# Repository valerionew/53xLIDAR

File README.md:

# 53xLIDAR

## Overview
Project for an opensource, all-in-one, solid state lidar.  
The lidar is made with 16 **VL53L1x** Time-of-flight IR ranging sensors.  

The sensors are operated by an **STM32F411RE** on two separate I2C buses, one for sensor 1-8, the other for 9-16. 
The XSHUTs are shared between two sensors on the two different I2C buses, while the sensors interrupts are separate for each sensor.   
For future use, there is an **LSM9DS1**, 9 DOF inertial sensor onboard.  

The lidar outputs the data via a virtual com port from the native Micro-USB, or via a 3.3V UART on a 4 pin JST-PH connector.  
Power (5V 100mA) is provided through the USB or via the 4 pin uart connector.

## Hardware
The hardware is designed in KiCAD and released under CERN OHL licence. 

It is formed by 16 sensor daughter boards, arranged in a 32 modules panel (only half panel is needed for one lidar, but for manufacturing reasons is made as a 32 modules panel); a bottom board containing all the electronics; a top board which brings the I2C line to the sensors and adds mechanical strenght and protection to the sensors.

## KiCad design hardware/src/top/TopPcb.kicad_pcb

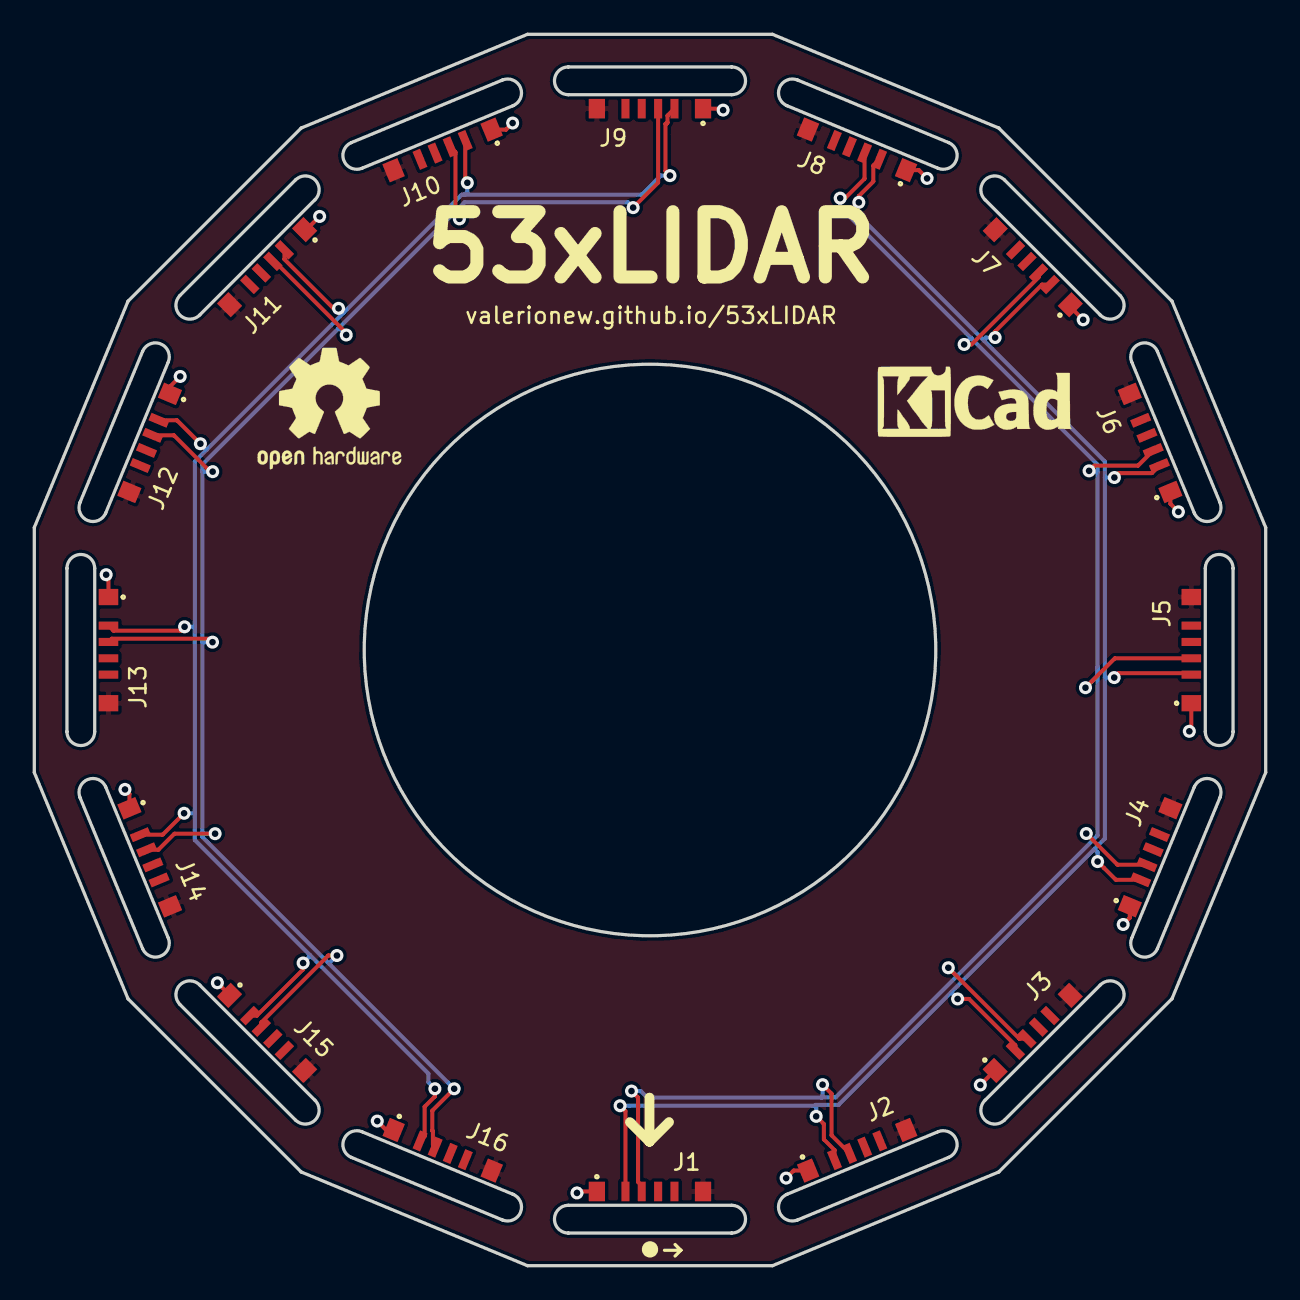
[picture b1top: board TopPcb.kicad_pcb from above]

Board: 2 copper layers, 75.4 x 75.4 mm, 16 parts (0 on the bottom side), 6 nets.

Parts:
J1, J2, J3, J4, J5, J6, J7, J8, J9, J10, J11, J12, J13, J14, J15, J16: CONN_01X06; CONN

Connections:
+3V3: J1.1, J2.1, J3.1, J4.1, J5.1, J6.1, J7.1, J8.1, J9.1, J10.1, J11.1, J12.1, J13.1, J14.1, J15.1, J16.1
GND: J1.6, J2.6, J3.6, J4.6, J5.6, J6.6, J7.6, J8.6, J9.6, J10.6, J11.6, J12.6, J13.6, J14.6, J15.6, J16.6
SCL1: J1.3, J2.3, J3.3, J4.3, J5.3, J6.3, J7.3, J8.3
SCL2: J9.3, J10.3, J11.3, J12.3, J13.3, J14.3, J15.3, J16.3
SDA1: J1.2, J2.2, J3.2, J4.2, J5.2, J6.2, J7.2, J8.2
SDA2: J9.2, J10.2, J11.2, J12.2, J13.2, J14.2, J15.2, J16.2

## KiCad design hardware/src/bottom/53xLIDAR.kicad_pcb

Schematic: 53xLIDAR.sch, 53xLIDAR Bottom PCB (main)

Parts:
BOOT0_TP1: BOOT0; Measurement_Point_Round-SMD-Pad_Small
C1, C2, C3, C4, C5, C6, C7, C8, C12, C13, C17, C20, C22: 100n; C_0402
C9, C14, C15, C16, C18, C19: 4.7u; C_0805_HandSoldering
C10, C11: 15p; C_0402
C21: 10n 16V; C_0805_HandSoldering
D1: USL1M; D_SOD-123
J1, J2, J3, J4, J5, J6, J7, J8, J9, J10, J11, J12, J13, J14, J15, J16: CONN_01X06; CONN
J17: USB_OTG; miniusb_MUSB-B5-S-VT-TSMT-1
J18: UART_EXT; JST_PH_B4B-PH-SM4-TB_04x2.00mm_Straight
J19: I2C1_DEBUG; Pad_test_SMD_1x03_Pitch1.27mm
J20: I2C2_DEBUG; Pad_test_SMD_1x03_Pitch1.27mm
J21: UART_DEBUG; Pad_test_SMD_1x03_Pitch1.27mm
J22: SWD; Pin_Header_Straight_1x04_Pitch2.54mm
J23: SPI1_EXT; JST_PH_B6B-PH-SM4-TB_06x2.00mm_Straight
J25: GS3
R1: 10k; R_0402
U1, U2, U3, U4: WS2812S; LED_WS2812-PLCC6
U5: STM32F411RETx; LQFP-64_10x10mm_Pitch0.5mm
U6: MPU-9250; QFN-24_3x3mm_Pitch0.4mm
U7: KF33_DPAK; TO-252-2
U8: LSM9DS1; LGA-24L_3x3.5mm_Pitch0.43mm
Y1: 24MHz SR PASSIVES 3225-24M-SR; Crystal_SMD_3225-4pin_3.2x2.5mm

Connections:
+3V3: C5.1, C6.1, C7.1, C8.1, C12.2, C15.1, C16.1, C17.1, C18.1, C19.1, C20.2, J1.1, J2.1, J3.1, J4.1, J5.1, J6.1, J7.1, J8.1, J9.1, J10.1, J11.1, J12.1, J13.1, J14.1, J15.1, J16.1, J22.1, J23.1, J25.1, U5.13 (VREF+), U5.19 (VDD), U5.32 (VDD), U5.48 (VDD), U5.64 (VDD), U6.1, U6.8, U6.13, U7.3 (VO), U8.1, U8.3, U8.22, U8.23
EXT_CS: J23.5, U5.53 (PC12/I2S3_SD/SDIO_CK/SPI3_MOSI)
IMU_CS: U5.61 (I2C1_SCL/I2C3_SDA/I2S5_SD/SDIO_D4/SPI5_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), U6.22, U8.7
IMU_CS_MAG: U5.52 (PC11/ADC1_EXTI11/I2S3_ext_SD/SDIO_D3/SP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), U8.8
IMU_DRDY_MAG: U5.34 (I2S2_CK/I2S4_CK/SPI2_SCK/SPI4_SCK/TIM1_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), U8.9
IMU_INT: U5.54 (PD2/SDIO_CMD/TIM3_ETR), U6.12, U8.11
IMU_INT_MAG: U5.51 (PC10/I2S3_CK/SDIO_D2/SPI3_SCK), U8.10
INT1: J1.5, U5.24 (PC4/ADC1_IN14)
INT2: J2.5, U5.25 (PC5/ADC1_IN15)
INT3: J3.5, U5.26 (ADC1_IN8/I2S5_CK/SPI5_SCK/TIM1_CH2N/TIM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)
INT4: J4.5, U5.27 (ADC1_IN9/I2S5_WS/SPI5_NSS/TIM1_CH3N/TIM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)
INT5: J5.5, U5.28 (BOOT1/PB2)
INT6: J6.5, U5.35 (I2S2_ext_SD/SDIO_D6/SPI2_MISO/TIM1_CH2N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)
INT7: J7.5, U5.36 (ADC1_EXTI15/I2S2_SD/RTC_REFIN/SDIO_CK/S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)
INT8: J8.5, U5.37 (PC6/I2S2_MCK/SDIO_D6/TIM3_CH1/USART6_TX)
INT9: J9.5, U5.38 (PC7/I2S2_CK/I2S3_MCK/SDIO_D7/SPI2_SCK/T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)
INT10: J10.5, U5.39 (PC8/SDIO_D0/TIM3_CH3/USART6_CK)
INT11: J11.5, U5.4 (PC15/ADC1_EXTI15/RCC_OSC32_OUT)
INT12: J12.5, U5.2 (PC13/ANTI_TAMP/RTC_AF1)
INT13: J13.5, U5.3 (PC14/RCC_OSC32_IN)
INT14: J14.5, U5.62 (I2C1_SDA/I2C2_SDA/I2S2_WS/SDIO_D5/SPI2_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)
INT15: J15.5, U5.14 (ADC1_IN0/SYS_WKUP/TIM2_CH1/TIM2_ETR/TIM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)
INT16: J16.5, U5.15 (ADC1_IN1/I2S4_SD/SPI4_MOSI/TIM2_CH2/TIM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)
unnamed: BOOT0_TP1.1, R1.1, U5.60 (BOOT0)
unnamed: C9.2, U5.30 (VCAP1)
unnamed: C10.1, U5.5 (PH0/RCC_OSC_IN), Y1.3
unnamed: C11.1, U5.6 (PH1/RCC_OSC_OUT), Y1.1
unnamed: C13.2, U6.10
unnamed: C21.2, U8.21
unnamed: C22.1, U8.24
unnamed: D1.1, U1.3
unnamed: J25.2, U8.13
unnamed: U1.1, U2.2
unnamed: U2.1, U3.2
unnamed: U3.1, U4.2
SCL1: J1.3, J2.3, J3.3, J4.3, J5.3, J6.3, J7.3, J8.3, J19.1, U5.58 (I2C1_SCL/TIM4_CH1/USART1_TX/PB6)
SCL2: J9.3, J10.3, J11.3, J12.3, J13.3, J14.3, J15.3, J16.3, J20.1, U5.29 (I2C2_SCL/I2S2_CK/I2S3_MCK/SDIO_D7/SPI2_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)
SCL_IMU: J23.4, U5.33 (I2C2_SMBA/I2S2_WS/I2S3_CK/I2S4_WS/SPI2_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), U5.41 (I2C3_SCL/RCC_MCO_1/SDIO_D1/TIM1_CH1/USA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), U6.23, U8.2
SDA1: J1.2, J2.2, J3.2, J4.2, J5.2, J6.2, J7.2, J8.2, J19.2, U5.59 (I2C1_SDA/SDIO_D0/TIM4_CH2/USART1_RX/PB7)
SDA2: J9.2, J10.2, J11.2, J12.2, J13.2, J14.2, J15.2, J16.2, J20.2, U5.55 (I2C2_SDA/I2S1_CK/I2S3_CK/SPI1_SCK/SPI3_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)
SDA_IMU: J23.2, U5.40 (PC9/I2C3_SDA/I2S_CKIN/RCC_MCO_2/SDIO_D1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), U5.57 (I2C1_SMBA/I2S1_SD/I2S3_SD/SDIO_D3/SPI1_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), U6.24, U8.4
SPI1_MISO: J23.3, U5.56 (I2C3_SDA/I2S3_ext_SD/SDIO_D0/SPI1_MISO/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), U6.9, U8.5, U8.6
SWCLK_PROGRAMMING: J22.3, U5.49 (SYS_JTCK-SWCLK/PA14)
SWDIO_PROGRAMMING: J22.2, U5.46 (SYS_JTMS-SWDIO/PA13)
USART_DEBUG_RX: J21.1, U5.17 (ADC1_IN3/I2S2_MCK/TIM2_CH4/TIM5_CH4/TIM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)
USART_DEBUG_TX: J21.2, U5.16 (ADC1_IN2/I2S_CKIN/TIM2_CH3/TIM5_CH3/TIM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)
USART_EXT_RX: J18.2, U5.43 (I2S5_SD/SPI5_MOSI/TIM1_CH3/USART1_RX/US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)
USART_EXT_TX: J18.1, U5.42 (I2C3_SMBA/SDIO_D2/TIM1_CH2/USART1_TX/US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)
USB_D+: J17.3, U5.45 (SPI5_MISO/TIM1_ETR/USART1_RTS/USART6_RX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)
USB_D-: J17.2, U5.44 (ADC1_EXTI11/SPI4_MISO/TIM1_CH4/USART1_C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)
USB_VBUS: C1.1, C2.1, C3.1, C4.1, C14.1, D1.2, J17.1, J18.3, U1.5, U2.3, U2.5, U3.3, U3.5, U4.3, U4.5, U7.1 (VI)
WS2812S_DATA: U1.2, U5.50 (ADC1_EXTI15/I2S1_WS/I2S3_WS/SPI1_NSS/SP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)
XSHUT1: J8.4, J9.4, U5.8 (PC0/ADC1_IN10)
XSHUT2: J7.4, J10.4, U5.9 (PC1/ADC1_IN11)
XSHUT3: J6.4, J11.4, U5.10 (PC2/ADC1_IN12/I2S2_ext_SD/SPI2_MISO)
XSHUT4: J5.4, J12.4, U5.11 (PC3/ADC1_IN13/I2S2_SD/SPI2_MOSI)
XSHUT5: J4.4, J13.4, U5.20 (ADC1_IN4/I2S1_WS/I2S3_WS/SPI1_NSS/SPI3_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)
XSHUT6: J3.4, J14.4, U5.21 (ADC1_IN5/I2S1_CK/SPI1_SCK/TIM2_CH1/TIM2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)
XSHUT7: J2.4, J15.4, U5.22 (ADC1_IN6/I2S2_MCK/SDIO_CMD/SPI1_MISO/TI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)
XSHUT8: J1.4, J16.4, U5.23 (ADC1_IN7/I2S1_SD/SPI1_MOSI/TIM1_CH1N/TI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)

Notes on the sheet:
SET THE UNUSED ONE TO HIGH IMPEDANCE

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
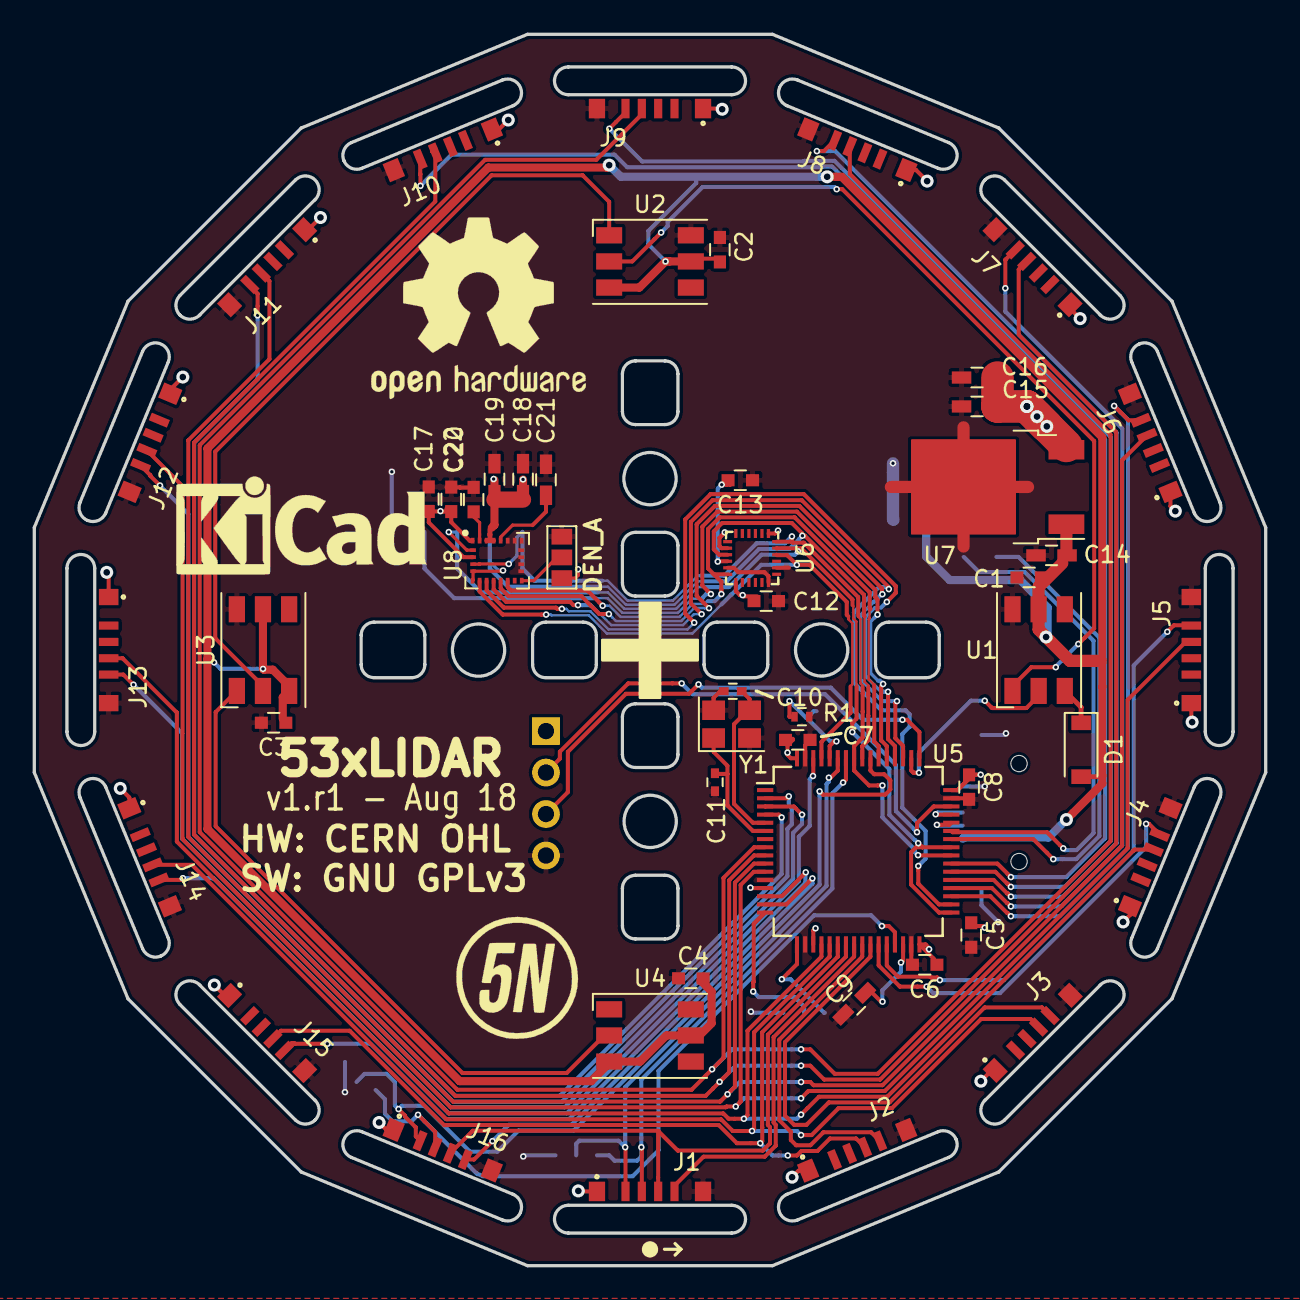
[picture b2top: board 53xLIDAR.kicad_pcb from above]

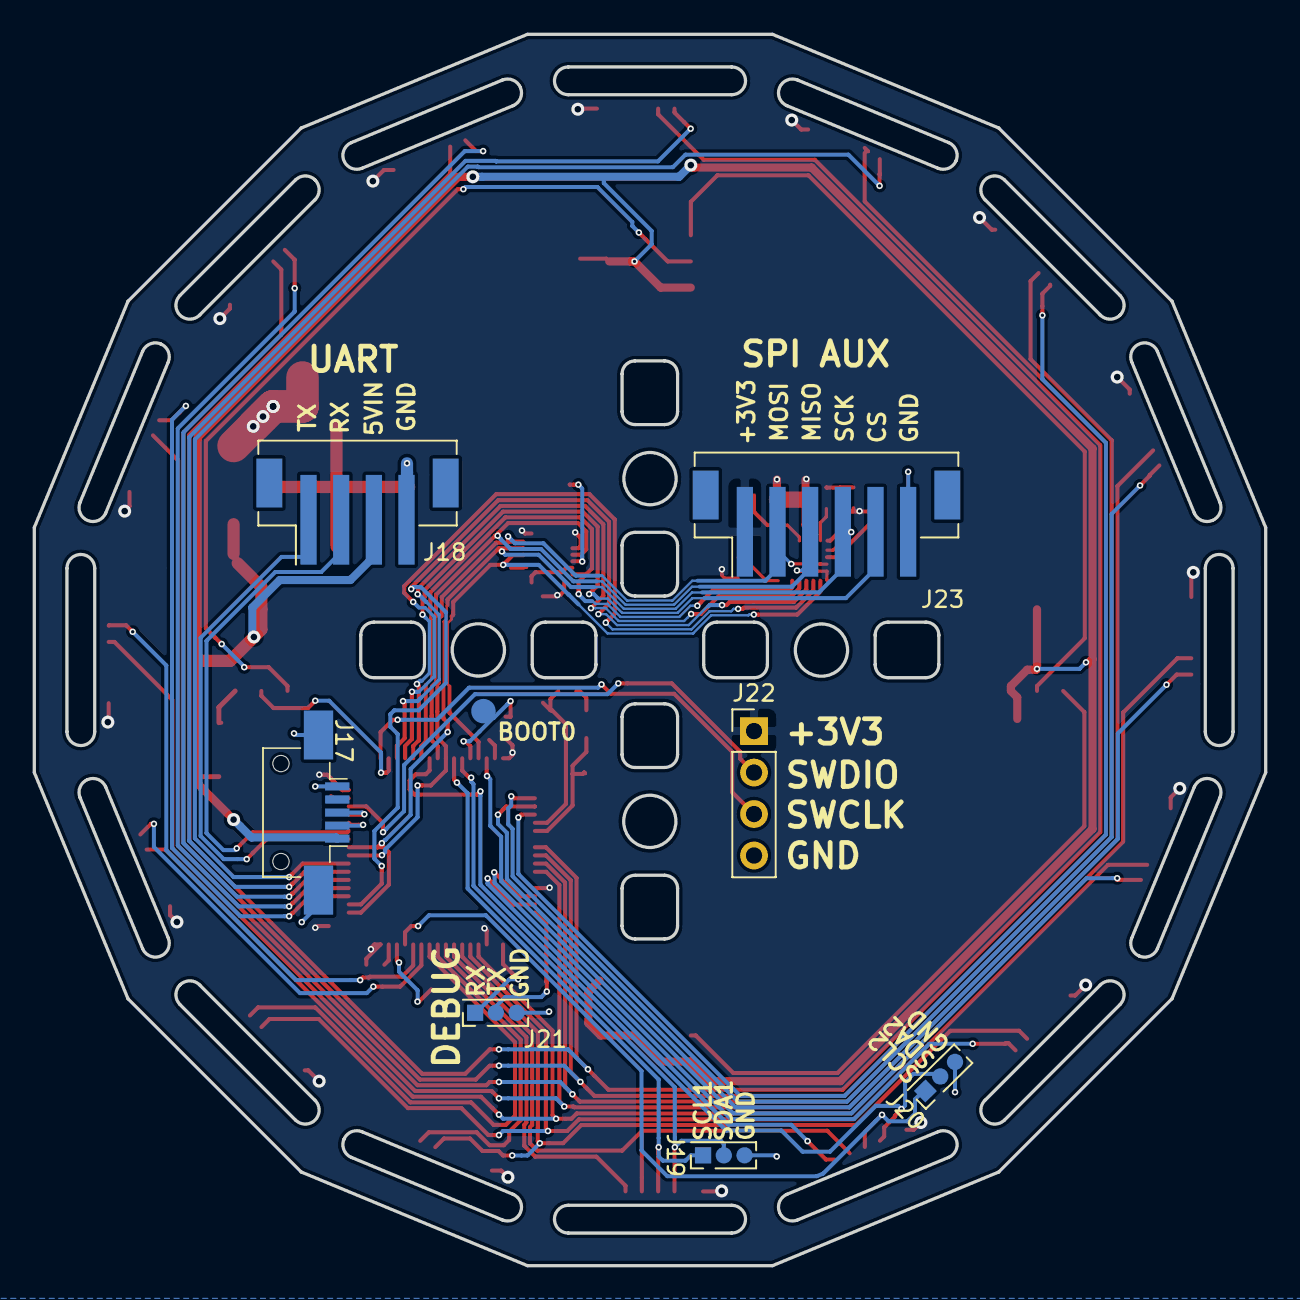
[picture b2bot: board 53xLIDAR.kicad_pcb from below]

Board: 2 copper layers, 75.4 x 75.4 mm, 58 parts (8 on the bottom side), 61 nets.

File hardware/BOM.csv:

Id,Ref,Package,Quantity,Value
1,C21,C_0603_HandSoldering,1,10n 16V
3,J17,USB_Mini-B_AdamTech_MUSB-B5-S-VT-TSMT-1_SMD_Vertical,1,USB_OTG
5,U5,LQFP-64_10x10mm_Pitch0.5mm,1,STM32F411RETx
7,D1,D_SOD-123,1,USL1M
8,J18,JST_PH_B4B-PH-SM4-TB_04x2.00mm_Straight,1,UART_EXT
9,J23,JST_PH_B6B-PH-SM4-TB_06x2.00mm_Straight,1,SPI1_EXT
10,U1;U2;U3;U4,LED_WS2812-PLCC6,4,WS2812S
11,U7,TO-252-2,1,KF33_DPAK
13,U6,QFN-24_3x3mm_Pitch0.4mm,1,MPU-9250
14,C10;C11,C_0402,2,15p
15,Y1,Crystal_SMD_3225-4pin_3.2x2.5mm,1,24MHz SR PASSIVES 3225-24M-SR
23,R1,R_0402,1,10k
24,U8,LGA-24L_3x3.5mm_Pitch0.43mm,1,LSM9DS1
25,C9;C14;C15;C16;C18;C19;C2_MODULESx16,C_0603_HandSoldering,22,4.7u
26,C1;C2;C3;C4;C5;C6;C7;C8;C12;C13;C17;C20;C22;C1_MODULESx16,C_0603,29,100n
28,R5_MODULESx16;R6_MODULESx16;R7_MODULESx16;R8_MODULESx16,R_0603,64,10k
30,U1_MODULES,ST_VL53L_HandSoldering,16,VL53L1X

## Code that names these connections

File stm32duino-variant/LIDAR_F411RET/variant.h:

/*
  Copyright (c) 2011 Arduino.  All right reserved.

  This library is free software; you can redistribute it and/or
  modify it under the terms of the GNU Lesser General Public
  License as published by the Free Software Foundation; either
  version 2.1 of the License, or (at your option) any later version.

  This library is distributed in the hope that it will be useful,
  but WITHOUT ANY WARRANTY; without even the implied warranty of
  MERCHANTABILITY or FITNESS FOR A PARTICULAR PURPOSE.
  See the GNU Lesser General Public License for more details.

  You should have received a copy of the GNU Lesser General Public
  License along with this library; if not, write to the Free Software
  Foundation, Inc., 51 Franklin St, Fifth Floor, Boston, MA  02110-1301  USA
*/

#ifndef _VARIANT_ARDUINO_STM32_
#define _VARIANT_ARDUINO_STM32_

/*----------------------------------------------------------------------------
 *        Headers
 *----------------------------------------------------------------------------*/
#include "PeripheralPins.h"

#ifdef __cplusplus
extern "C"{
#endif // __cplusplus

/*----------------------------------------------------------------------------
 *        Pins
 *----------------------------------------------------------------------------*/
extern const PinName digitalPin[];

enum {
  PA0,   //D0
  PA1,   //D1
  PA2,   //D2
  PA3,   //D3
  PA4,   //D4
  PA5,   //D5
  PA6,   //D6
  PA7,   //D7
  PA8,   //D8
  PA9,   //D9
  PA10,  //D10
  PA11,  //D11
  PA12,  //D12
  PA13,  //D13
  PA14,  //D14
  PA15,  //D15
  
  PB0,   //D16
  PB1,   //D17
  PB2,   //D18
  PB3,   //D19
  PB4,   //D20
  PB5,   //D21
  PB6,   //D22
  PB7,   //D23
  PB8,   //D24
  PB9,   //D25
  PB10,  //D26
  PB11,  //D27
  PB12,  //D28
  PB13,  //D29
  PB14,  //D30
  PB15,  //D31
  
  PC0,   //D32
  PC1,   //D33
  PC2,   //D34
  PC3,   //D35
  PC4,   //D36
  PC5,   //D37
  PC6,   //D38
  PC7,   //D39
  PC8,   //D40
  PC9,   //D41
  PC10,  //D42
  PC11,  //D43
  PC12,  //D44
  PC13,  //D45
  PC14,  //D46/A0
  PC15,  //D47/A1
  
  // Duplicated pins in order to be aligned with PinMapADC
  PC11a,  //D48/A2
  PC11b,  //D49/A3
  PC11c,  //D50/A4
  PC11d,  //D51/A5
  PC11e,  //D52/A6  = D11
  PC11f,  //D53/A7  = D12
  PC11g,  //D54/A8  = D28
  PC11h,  //D55/A9  = D29
  PC11i,  //D56/A111 = D35
  PC11l,  //D57/A11 = D41
  PC11m,  //D58/A12 = D45
  PEND
};

// This must be a literal with the same value as PEND
#define NUM_DIGITAL_PINS        59
// This must be a literal with a value less than or equal to to MAX_ANALOG_INPUTS
#define NUM_ANALOG_INPUTS       13
#define NUM_ANALOG_FIRST        46

// On-board LED pin number
#define LED_BUILTIN             13
#define LED_GREEN               LED_BUILTIN

// On-board user button
#define USER_BTN                PC10

// Timer Definitions
// Do not use timer used by PWM pins when possible. See PinMap_PWM.
#define TIMER_TONE              TIM10

// Do not use basic timer: OC is required
#define TIMER_SERVO             TIM2  //TODO: advanced-control timers don't work

// UART Definitions
#define SERIAL_UART_INSTANCE    2 //Connected to ST-Link
// Default pin used for 'Serial' instance (ex: ST-Link)
// Mandatory for Firmata
#define PIN_SERIAL_RX           PA3
#define PIN_SERIAL_TX           PA2

#ifdef __cplusplus
} // extern "C"
#endif
/*----------------------------------------------------------------------------
 *        Arduino objects - C++ only
 *----------------------------------------------------------------------------*/

#ifdef __cplusplus
// These serial port names are intended to allow libraries and architecture-neutral
// sketches to automatically default to the correct port name for a particular type
// of use.  For example, a GPS module would normally connect to SERIAL_PORT_HARDWARE_OPEN,
// the first hardware serial port whose RX/TX pins are not dedicated to another use.
//
// SERIAL_PORT_MONITOR        Port which normally prints to the Arduino Serial Monitor
//
// SERIAL_PORT_USBVIRTUAL     Port which is USB virtual serial
//
// SERIAL_PORT_LINUXBRIDGE    Port which connects to a Linux system via Bridge library
//
// SERIAL_PORT_HARDWARE       Hardware serial port, physical RX & TX pins.
//
// SERIAL_PORT_HARDWARE_OPEN  Hardware serial ports which are open for use.  Their RX & TX
//                            pins are NOT connected to anything by default.
#define SERIAL_PORT_MONITOR     Serial
#define SERIAL_PORT_HARDWARE    Serial
#endif

#endif /* _VARIANT_ARDUINO_STM32_ */

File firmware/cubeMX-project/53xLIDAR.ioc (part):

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Mcu.Name=STM32F411R(C-E)Tx
Mcu.Package=LQFP64
Mcu.UserName=STM32F411RETx
PA0-WKUP.Signal=GPIO_Input
PA1.Signal=GPIO_Input
PA10.Mode=Asynchronous
PA10.Signal=USART1_RX
PA11.Mode=Device_Only
PA11.Signal=USB_OTG_FS_DM
PA12.Mode=Device_Only
PA12.Signal=USB_OTG_FS_DP
PA13.Mode=Serial_Wire
PA13.Signal=SYS_JTMS-SWDIO
PA14.Mode=Serial_Wire
PA14.Signal=SYS_JTCK-SWCLK
PA15.Signal=GPIO_Output
PA2.Mode=Asynchronous
PA2.Signal=USART2_TX
PA3.Mode=Asynchronous
PA3.Signal=USART2_RX
PA4.Signal=GPIO_Output
PA5.Signal=GPIO_Output
PA6.Signal=GPIO_Output
PA7.Signal=GPIO_Output
PA8.Mode=I2C
PA8.Signal=I2C3_SCL
PA9.Mode=Asynchronous
PA9.Signal=USART1_TX
PB0.Signal=GPIO_Input
PB1.Signal=GPIO_Input
PB10.Mode=I2C
PB10.Signal=I2C2_SCL
PB12.Mode=Full_Duplex_Master
PB12.Signal=SPI3_SCK
PB14.Signal=GPIO_Input
PB15.Signal=GPIO_Input
PB2.Signal=GPIO_Input
PB3.Mode=I2C
PB3.Signal=I2C2_SDA
PB4.Mode=Full_Duplex_Master
PB4.Signal=SPI3_MISO
PB5.Mode=Full_Duplex_Master
PB5.Signal=SPI3_MOSI
PB6.Mode=I2C
PB6.Signal=I2C1_SCL
PB7.Mode=I2C
PB7.Signal=I2C1_SDA
PB8.Signal=GPIO_Output
PB9.Signal=GPIO_Input
PC0.Signal=GPIO_Output
PC1.Signal=GPIO_Output
PC12.Signal=GPIO_Output
PC13-ANTI_TAMP.Signal=GPIO_Input
PC14-OSC32_IN.Signal=GPIO_Input
PC15-OSC32_OUT.Signal=GPIO_Input
PC2.Signal=GPIO_Output
PC3.Signal=GPIO_Output
PC4.Signal=GPIO_Input
PC5.Signal=GPIO_Input
PC6.Signal=GPIO_Input
PC7.Signal=GPIO_Input
PC8.Signal=GPIO_Input
PC9.Mode=I2C
PC9.Signal=I2C3_SDA
PD2.Signal=GPIO_Input
PH0\ -\ OSC_IN.Mode=HSE-External-Oscillator
PH0\ -\ OSC_IN.Signal=RCC_OSC_IN
PH1\ -\ OSC_OUT.Mode=HSE-External-Oscillator
PH1\ -\ OSC_OUT.Signal=RCC_OSC_OUT
RCC.HSE_VALUE=24000000
RCC.SYSCLKFreq_VALUE=96000000
RCC.SYSCLKSource=RCC_SYSCLKSOURCE_PLLCLK
board=custom

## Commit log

2018-08-02 Set theme jekyll-theme-cayman
2018-08-06 Added gitignore
2018-08-06 readme
2018-08-06 cubeMX raw project, exported as SW4STM32, initial stm32duino variant creation. come bug in board.txt, it does not find the conf file...
2018-08-06 moving firmware in it's folder
2018-08-06 fix markdown extension
2018-08-07 fixed stencil for CONN footprints
2018-08-07 fixed manufactury requirements
2018-08-07 Added 3Ds
2018-08-10 added LSM9DS1, revision 1
2018-08-10 Revision 1
2018-08-10 Bom optimization
2018-08-10 New gerbers
2018-08-11 Fixed bugs introduced in rev1
2018-08-11 Removed IMU axes on silkscreen as they are no longer consistent with the two IMUs
2018-08-14 Added BOM
2018-09-22 added testing firmware
2018-09-22 removed older code
2018-09-30 added ws2812 support, and different other modification to try make this sensors stable
2018-10-01 fixed to create hex in linux
2018-10-03 added visualization in processing
2018-10-07 added quadratic view, hardcoded for FullHD screen, added fading, added averange
2020-04-04 moved code in the right USER CODE tokens
2020-04-04 Moved to the new STM32CubeIDE environment, new VL53L1 APIs not working yet
2020-04-05 updated platform to work with stm32f4
2020-04-05 Updated the main to the new firmware. Not tested
2020-04-05 fixed compilation error, maybe
2020-04-05 fixed for real, now it compiles
2020-06-20 Update PRODUCT
2021-10-11 added images

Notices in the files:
hardware/src/bottom/53xLIDAR.kicad_pcb:
HW: CERN OHL
SW: GNU GPLv3
hardware/src/bottom/53xLIDAR.sch:
LICENSE: CERN OHL
